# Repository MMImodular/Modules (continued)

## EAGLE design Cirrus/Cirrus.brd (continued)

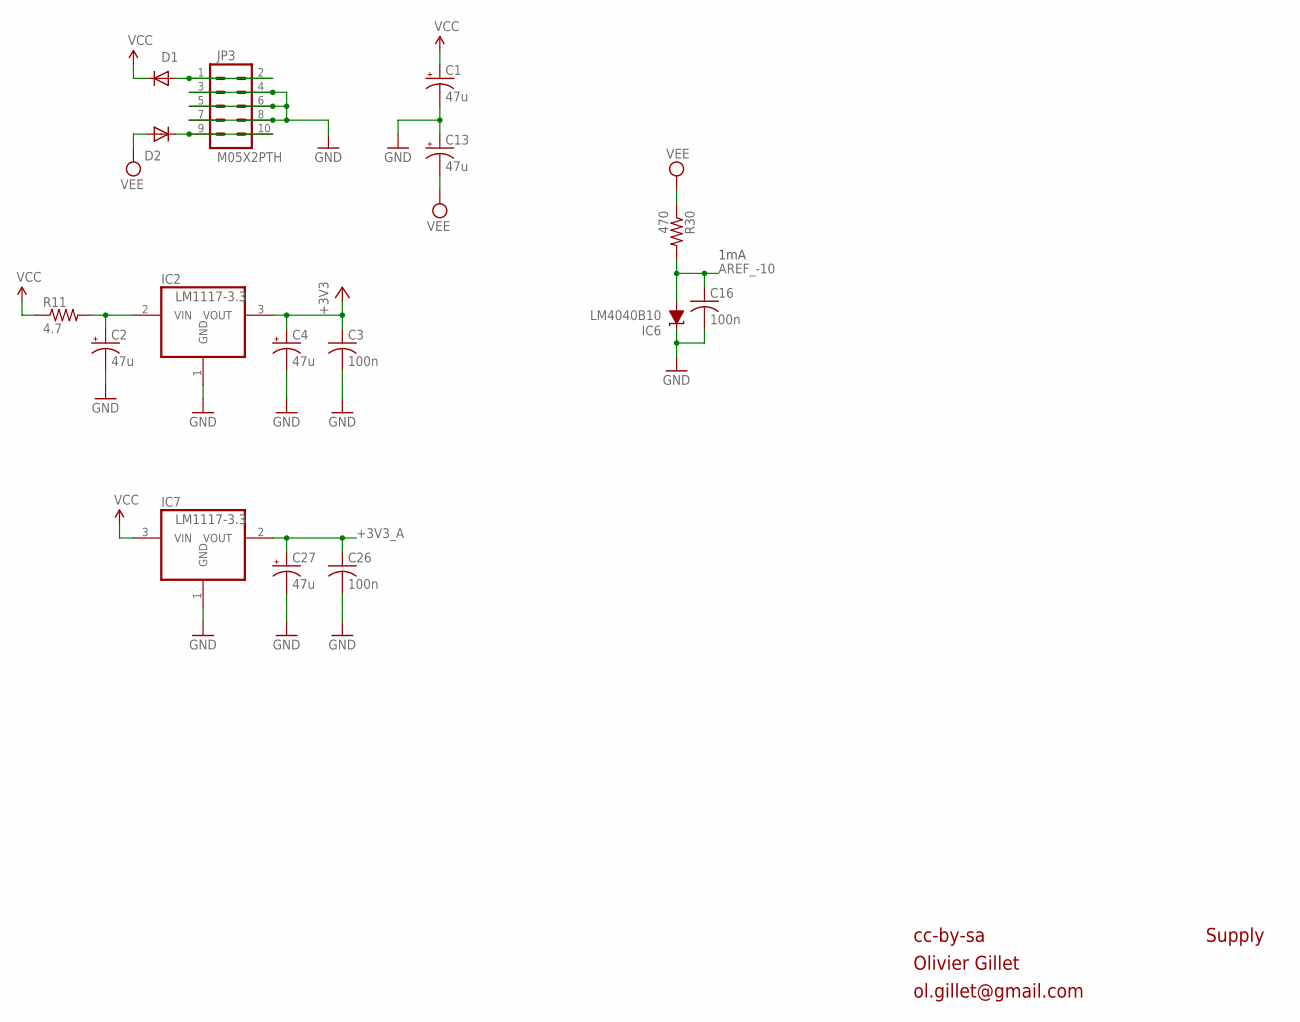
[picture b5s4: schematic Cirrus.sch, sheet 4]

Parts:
C1, C2, C4, C13, C27: 47u; PANASONIC_D
C3, C16, C26: 100n; C0603
D1, D2: 1N5819HW; SOD123
IC2: LM1117-3.3; TO252
IC6: LM4040B10; DBZ_R-PDSO-G3
IC7: LM1117-3.3; SOT223
JP3: M05X2PTH; AVR_ICSP
R11: 4.7; R1206
R30: 470; R0603

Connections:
+3V3: C3.1, C4.+, IC2.3 (VOUT); also elsewhere on the board
+3V3_A: C26.1, C27.+, IC7.2 (VOUT); also elsewhere on the board
AREF_-10: C16.1, IC6.2 (A), R30.2; also elsewhere on the board
GND: C1.-, C2.-, C3.2, C4.-, C13.+, C16.2, C26.2, C27.-, IC2.1 (GND), IC6.1 (C), IC7.1 (GND), JP3.3, JP3.4, JP3.5, JP3.6, JP3.7, JP3.8; also elsewhere on the board
unnamed: C2.+, IC2.2 (VIN), R11.2
unnamed: D1.A, JP3.1, JP3.2
unnamed: D2.C, JP3.9, JP3.10
VCC: C1.+, D1.C, IC7.3 (VIN), R11.1; also elsewhere on the board
VEE: C13.-, D2.A, R30.1; also elsewhere on the board

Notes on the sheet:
1mA
cc-by-sa
Olivier Gillet
ol.gillet@gmail.com
Supply

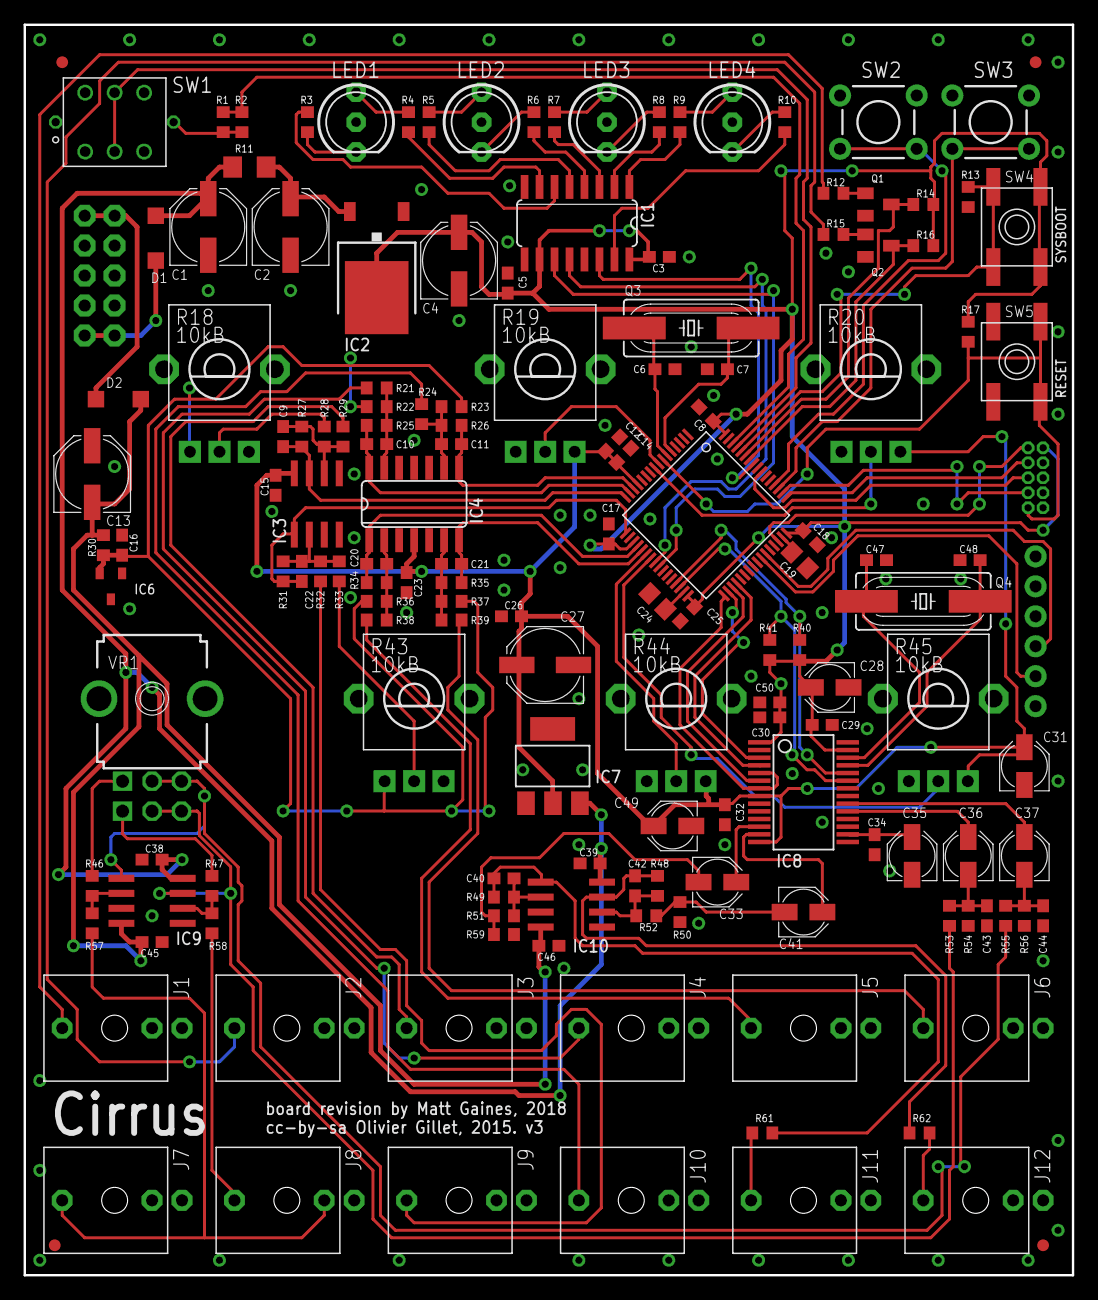
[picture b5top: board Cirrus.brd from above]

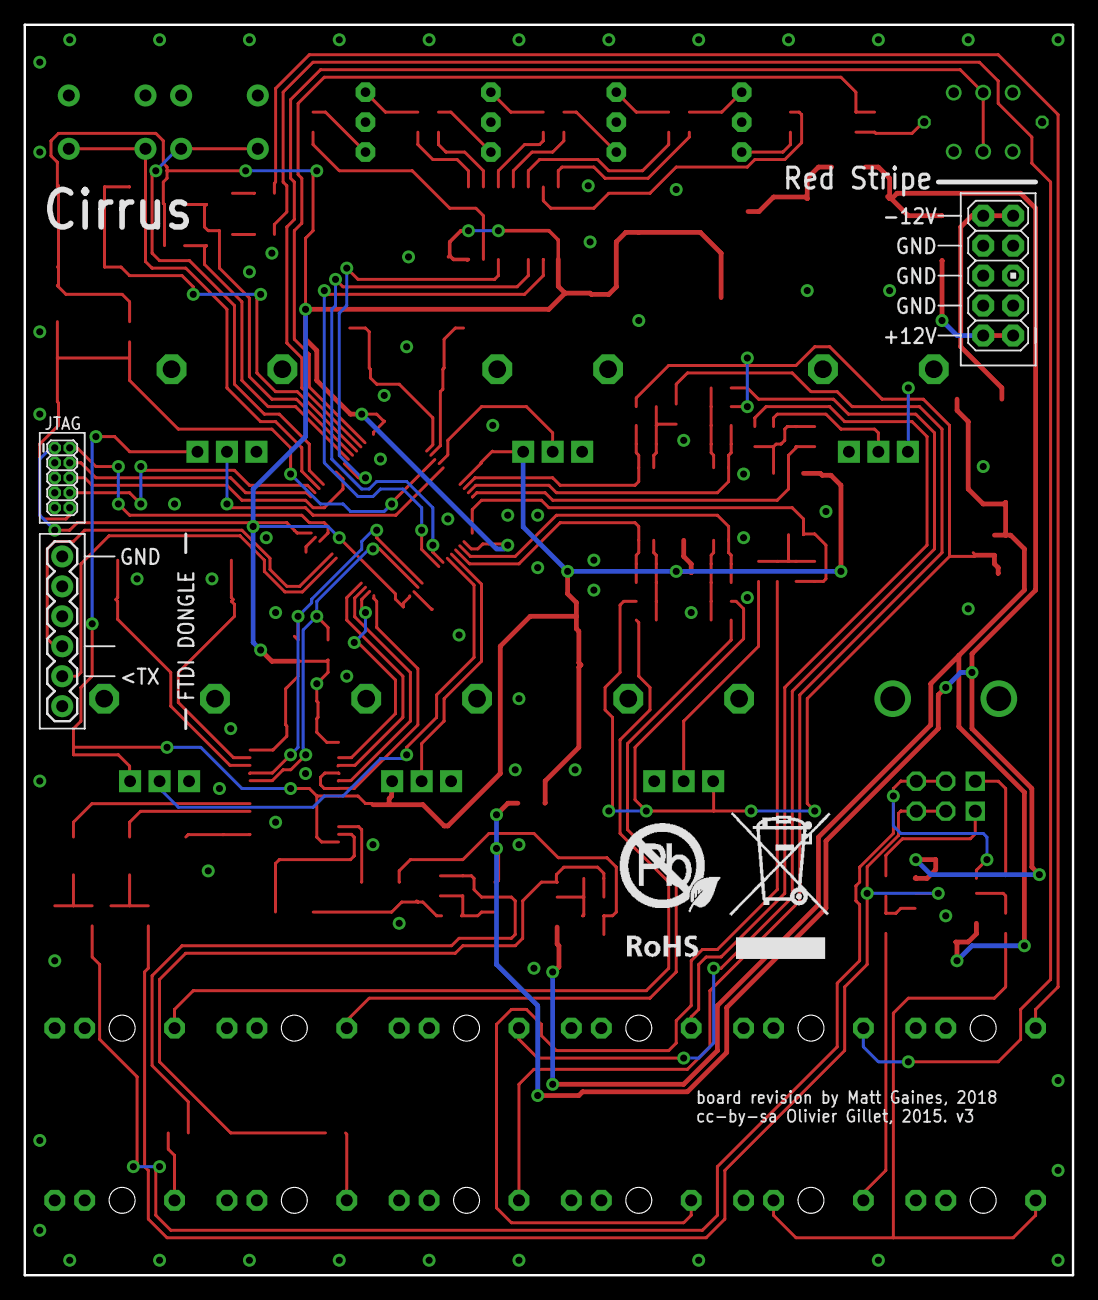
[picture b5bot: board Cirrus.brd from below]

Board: 2 copper layers, 88.9 x 106.0 mm, 156 parts (4 on the bottom side), 106 nets.

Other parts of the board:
U$2: ROHS_BIG

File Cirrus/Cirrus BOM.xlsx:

Qty | Value | Device | Package | Parts | Description | SPICEPREFIX | Column1
2 |  | EVQQ2 | EVQ-Q2 | SW4, SW5 | SMT 6mm switch, EVQQ2 series
1 |  | M06SIP | 1X06 | JP1 | Header 6
2 |  | TAC_SWITCHPTH | TACTILE-PTH | SW2, SW3 | Momentary Switch
2 | 1.0k | R-US_R0603 | R0603 | R61, R62 | RESISTOR, American symbol
8 | 100k | R-US_R0603 | R0603 | R12, R15, R21, R24, R29, R32, R38, R39 | RESISTOR, American symbol
19 | 100n | C-USC0603 | C0603 | C3, C5, C8, C14, C15, C16, C17, C18, C23, C25, C26, C29, C30, C32, C34, C38, C3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 | CAPACITOR, American symbol
4 | 10k | R-US_R0603 | R0603 | R13, R14, R16, R17 | RESISTOR, American symbol
6 | 10kB | POT_USVERTICAL_PS | ALPS_POT_VERTICAL_PS | R18, R19, R20, R43, R44, R45
7 | 10u | CPOL-USB | PANASONIC_B | C28, C31, C33, C35, C36, C37, C41 | POLARIZED CAPACITOR, American symbol
1 | 10u | CPOL-USB | PANASONIC_B | C49 | POLARIZED CAPACITOR, American symbol | C
1 | 12.288MHz | CRYSTALHC49UP | HC49UP | Q4 | CRYSTAL
1 | 180k | R-US_R0603 | R0603 | R36 | RESISTOR, American symbol
6 | 18p | C-USC0603 | C0603 | C6, C7, C40, C42, C47, C48 | CAPACITOR, American symbol
2 | 1N5819HW | DIODE-SOD123 | SOD123 | D1, D2 | DIODE
6 | 1n | C-USC0603 | C0603 | C9, C10, C11, C20, C21, C22 | CAPACITOR, American symbol
2 | 1u | C-USC0603 | C0603 | C12, C50 | CAPACITOR, American symbol
2 | 2.2k | R-US_R0603 | R0603 | R40, R41 | RESISTOR, American symbol
2 | 2.2u | C-USC0805 | C0805 | C19, C24 | CAPACITOR, American symbol
5 | 200k | R-US_R0603 | R0603 | R22, R23, R28, R33, R37 | RESISTOR, American symbol
2 | 220p | C-USC0603 | C0603 | C43, C44 | CAPACITOR, American symbol
2 | 22k | R-US_R0603 | R0603 | R57, R58 | RESISTOR, American symbol
2 | 3.3k | R-US_R0603 | R0603 | R46, R47 | RESISTOR, American symbol
3 | 33k | R-US_R0603 | R0603 | R25, R26, R35 | RESISTOR, American symbol
4 | 39k | R-US_R0603 | R0603 | R48, R49, R50, R59 | RESISTOR, American symbol
1 | 4.7 | R-US_R1206 | R1206 | R11 | RESISTOR, American symbol
1 | 470 | R-US_R0603 | R0603 | R30 | RESISTOR, American symbol
1 | 47k | R-US_R0603 | R0603 | R34 | RESISTOR, American symbol
5 | 47u | CPOL-USD | PANASONIC_D | C1, C2, C4, C13, C27 | POLARIZED CAPACITOR, American symbol
6 | 5.6k | R-US_R0603 | R0603 | R51, R52, R53, R54, R55, R56 | RESISTOR, American symbol
1 | 50kA | ALPHA-9MM-DUALPOT | DUAL_9MM_SNAP-IN_POT | VR1 | 9mm vertical snap-in pot, Alpha / Panasonic style, with a connection to the met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
2 | 66.5k | R-US_R0603 | R0603 | R27, R31 | RESISTOR, American symbol
10 | 68 | R-US_R0603 | R0603 | R1, R2, R3, R4, R5, R6, R7, R8, R9, R10 | RESISTOR, American symbol
1 | 74HC595D | 74HC595D | SO16 | IC1 | 8-bit SHIFT REGISTER, output latch
1 | 8MHz | CRYSTALHC49UP | HC49UP | Q3 | CRYSTAL
4 | FIDUCIAL1X2 | FIDUCIAL1X2 | FIDUCIAL-1X2 | F1, F2, F3, F4 | Fiducial Alignment Points
1 | LM1117-3.3 | REG1117 | SOT223 | IC7 | 800mA and 1A Low Dropout (LDO) Positive Regulator
1 | LM1117-3.3 | REG1117T | TO252 | IC2 | 800mA and 1A Low Dropout (LDO) Positive Regulator
1 | LM4040B10 | LM4041B12DBZ | DBZ_R-PDSO-G3 | IC6 | PRECISION MICROPOWER SHUNT VOLTAGE REFERENCE
1 | LP4OA1PBCT | LP4OA1PBCT | LP4OA1PBCT | SW1
1 | M05X2MINIJTAG | M05X2MINIJTAG | 2X5-1.27 | JP2 | Header 5x2
1 | M05X2PTH | M05X2PTH | AVR_ICSP | JP3 | Header 5x2
1 | MCP6002 | TL072D | SO08 | IC3 | OP AMP
1 | MCP6004 | TL074D | SO14 | IC4 | OP AMP
2 | MMBT3904 | MMBT3904LT1-NPN-SOT23-BEC | SOT23-BEC | Q1, Q2 | NPN Transistror
12 | PJ301_THONKICONN6 | PJ301_THONKICONN6 | WQP_PJ_301M6 | J1, J2, J3, J4, J5, J6, J7, J8, J9, J10, J11, J12
1 | STM32F405RGT6 | STM32F20X | TQFP-10X10-64 | IC5
2 | TL072D | TL072D | SO08 | IC9, IC10 | OP AMP
1 | WM8731 | WM8731 | SSOP28 | IC8
4 | WP59EGW | LED-BICOLOR-THROUGHHOLE5MM | LED-BICOLOR-THROUGHHOLE-5MM | LED1, LED2, LED3, LED4

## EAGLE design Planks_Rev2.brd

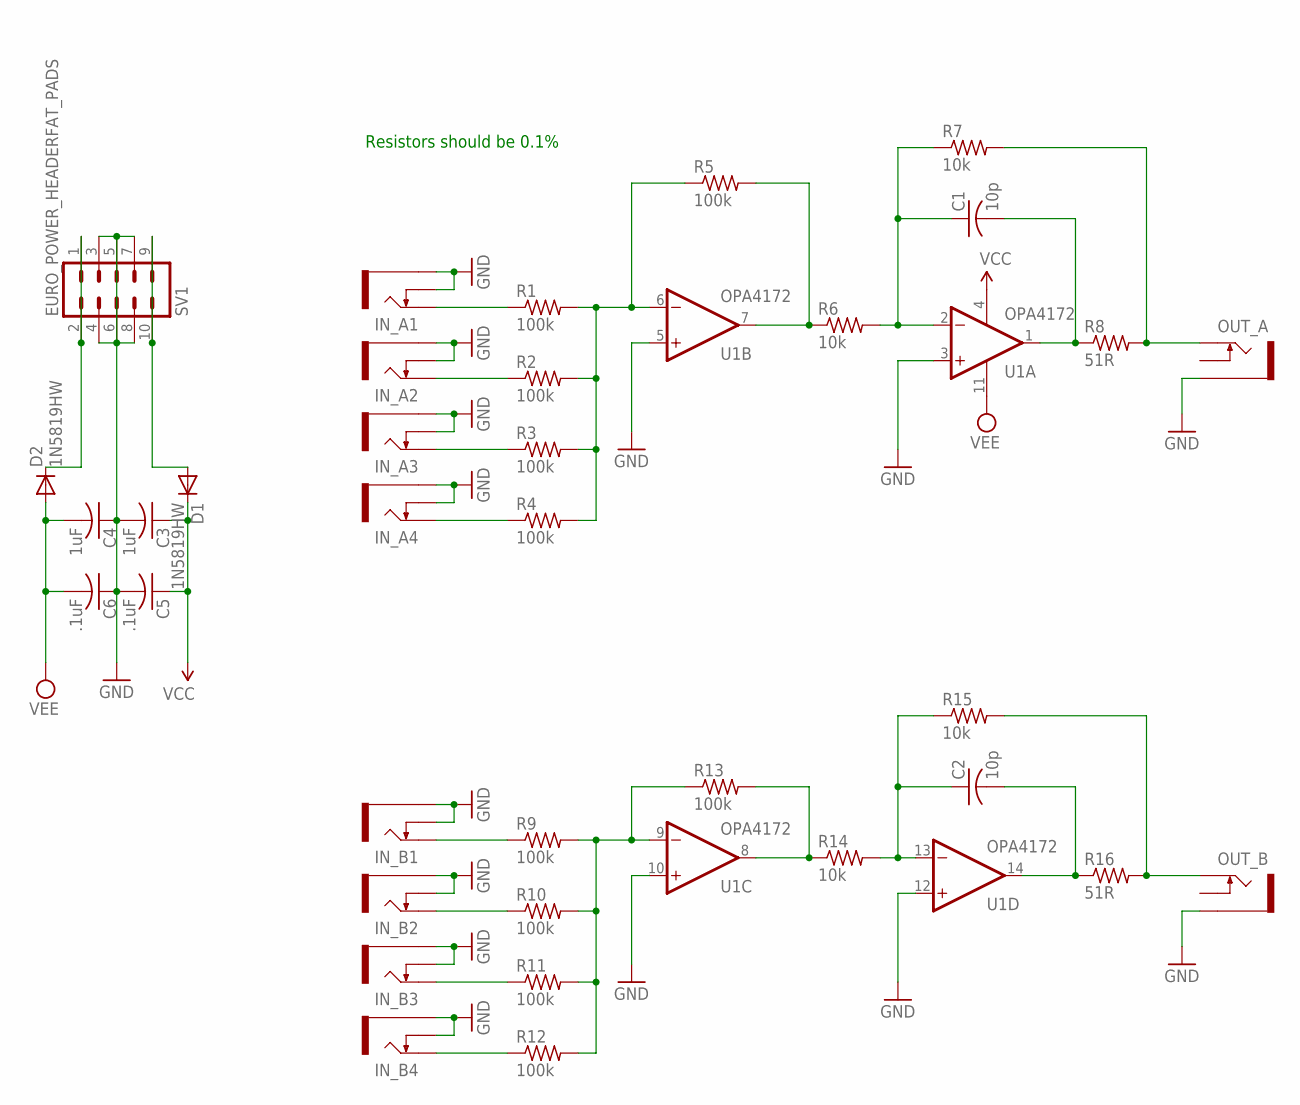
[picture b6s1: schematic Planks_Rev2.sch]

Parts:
C1, C2: 10p; C0603
C3, C4: 1uF; C0805
C5, C6: .1uF; C0603
D1, D2: 1N5819HW; SOD123
IN_A1, IN_A2, IN_A3, IN_A4: THONKICONNNEW; WQP-PJ301M-12_JACK
IN_B1, IN_B2, IN_B3, IN_B4: THONKICONNNEW; WQP-PJ301M-12_JACK
OUT_A: THONKICONNNEW; WQP-PJ301M-12_JACK
OUT_B: THONKICONNNEW; WQP-PJ301M-12_JACK
R1, R2, R3, R4, R5, R9, R10, R11, R12, R13: 100k; R0603
R6, R7, R14, R15: 10k; R0603
R8, R16: 51R; R0603
SV1: EURO_POWER_HEADERFAT_PADS; EURO_PWR_HEADER_FAT
U1: OPA4172; SO14

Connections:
GND: C3.2, C4.1, C5.2, C6.1, IN_A1.P$2_SWITCH (SWITCH), IN_A1.P$3_SLEEVE (SLEEVE), IN_A2.P$2_SWITCH (SWITCH), IN_A2.P$3_SLEEVE (SLEEVE), IN_A3.P$2_SWITCH (SWITCH), IN_A3.P$3_SLEEVE (SLEEVE), IN_A4.P$2_SWITCH (SWITCH), IN_A4.P$3_SLEEVE (SLEEVE), IN_B1.P$2_SWITCH (SWITCH), IN_B1.P$3_SLEEVE (SLEEVE), IN_B2.P$2_SWITCH (SWITCH), IN_B2.P$3_SLEEVE (SLEEVE), IN_B3.P$2_SWITCH (SWITCH), IN_B3.P$3_SLEEVE (SLEEVE), IN_B4.P$2_SWITCH (SWITCH), IN_B4.P$3_SLEEVE (SLEEVE), OUT_A.P$3_SLEEVE (SLEEVE), OUT_B.P$3_SLEEVE (SLEEVE), SV1.3, SV1.4, SV1.5, SV1.6, SV1.7, SV1.8, U1.3 (+IN), U1.5 (+IN), U1.10 (+IN), U1.12 (+IN)
unnamed: IN_A1.P$1_TIP (TIP), R1.1
unnamed: IN_A4.P$1_TIP (TIP), R4.1
unnamed: IN_A3.P$1_TIP (TIP), R3.1
unnamed: IN_A2.P$1_TIP (TIP), R2.1
unnamed: R1.2, R2.2, R3.2, R4.2, R5.1, U1.6 (-IN)
unnamed: IN_B1.P$1_TIP (TIP), R9.1
unnamed: R5.2, R6.1, U1.7 (OUT)
unnamed: C1.1, R6.2, R7.1, U1.2 (-IN)
unnamed: IN_B4.P$1_TIP (TIP), R12.1
unnamed: C1.2, R8.1, U1.1 (OUT)
unnamed: OUT_A.P$1_TIP (TIP), R7.2, R8.2
unnamed: IN_B3.P$1_TIP (TIP), R11.1
unnamed: IN_B2.P$1_TIP (TIP), R10.1
unnamed: R9.2, R10.2, R11.2, R12.2, R13.1, U1.9 (-IN)
unnamed: R13.2, R14.1, U1.8 (OUT)
unnamed: C2.1, R14.2, R15.1, U1.13 (-IN)
unnamed: D1.A, SV1.9, SV1.10
unnamed: D2.C, SV1.1, SV1.2
unnamed: OUT_B.P$1_TIP (TIP), R15.2, R16.2
unnamed: C2.2, R16.1, U1.14 (OUT)
VCC: C3.1, C5.1, D1.C, U1.4 (V+)
VEE: C4.2, C6.2, D2.A, U1.11 (V-)

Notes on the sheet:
Resistors should be 0.1%

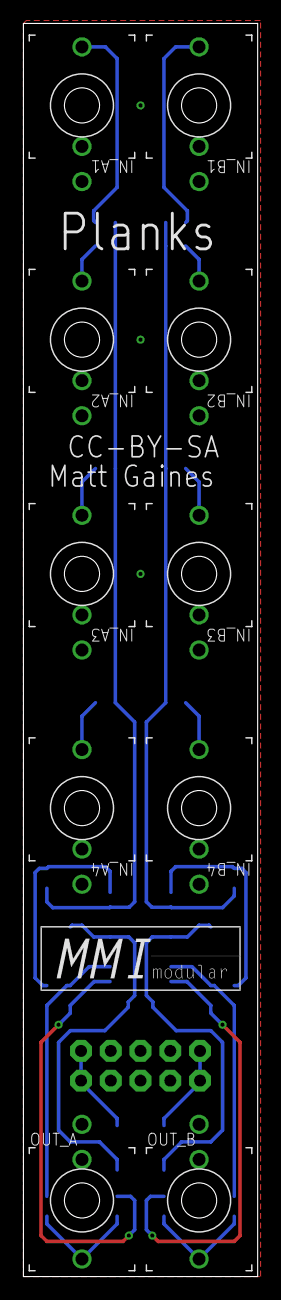
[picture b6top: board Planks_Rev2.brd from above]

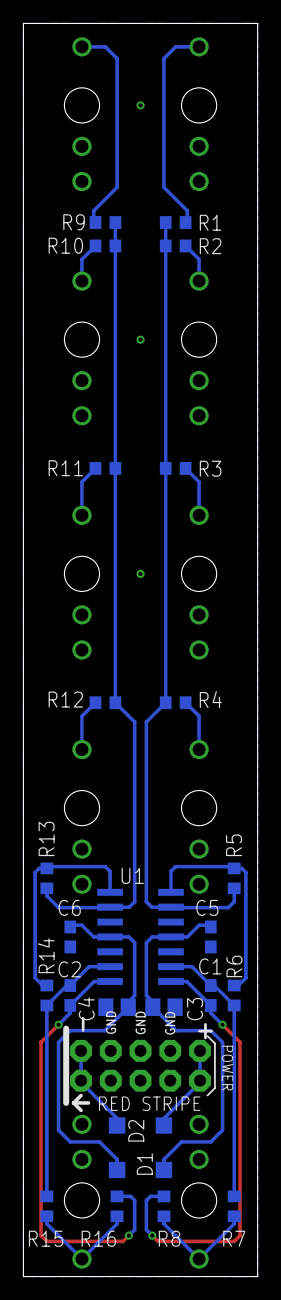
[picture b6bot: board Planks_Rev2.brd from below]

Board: 2 copper layers, 20.0 x 107.0 mm, 36 parts (26 on the bottom side), 23 nets.

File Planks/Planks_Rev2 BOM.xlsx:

Value | Package | Tolerance | Parts
100k | R0603 | 1E-3 | R1, R2, R3, R4, R5, R9, R10, R11, R12, R13
10k | R0603 | 1E-3 | R6, R7, R14, R15
51R | R0603 | 0.01 | R8, R16
1uF | C0805 | 0.1 | C3, C4
0.1uF | C0603 | 0.1 | C5, C6
10pF | C0603 | 0.05 | C1, C2
1N5819HW | SOD123 |  | D1, D2
OPA4172 | SO14 |  | U1
Thonkiconn | Thonkiconn |  | IN_A1, IN_A2, IN_A3, IN_A4, IN_B1, IN_B2, IN_B3, IN_B4, OUT_A, OUT_B

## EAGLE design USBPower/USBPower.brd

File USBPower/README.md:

# USB Power

* Based on Tom Whitwell's StupidUSBPower
* Integrated better DC-DC converter and removed frivolous features
* Rated to 416mA, capable of 110 ~ 140% overload with automatic recovery once fault condition is removed

This power supply is a low cost and low profile way to power a small lunchbox eurorack system. It is also a useful power supply for testing newly built modules outside of a larger system, especially if you must commute to your workspace.

___

The Meanwell DC-DC converter used in this power supply has a few important specifications to consider.
* Under full load, the DC-DC converter will draw upwards of 2300mA direct from your USB power brick. Make sure it can supply ~3A if you plan on running your PSU near the max current spec.
* Maximum load capacitance is 440uF per output. Approaching this may cause instability upon power-up. This needs more investigation on my part so I will update this list if I figure out more specific cases of instability.
* There is an under-voltage lockout implemented in this converter. It takes 4.4V to start the converter and it will shut down if it goes below 4.2V. This important because some users have experienced instability with USB cables that are incapable of supplying power. Voltage drop across the cable may be enough to go below 4.2V and result in a boot loop.

___
**Known module incompatibilities**

These are modules that people have plugged in and run in to boot looping issues with, despite the PSU operating normally otherwise. I do not have the ability to test each and every module that comes up, but if you own any of these I encourage testing it for yourself and sending me a message or email detailing what you found.

* Synthrotek 308 Distortion
* Jomox ModBase 09
* Strymon Magneto (works solo, but loops if other modules are present)

___
**Where to buy PCBs** 

* [Modular Addict](https://modularaddict.com/mmi-usbpower-pcb)

* [Pusherman](https://pushermanproductions.com/product/mmi-modular-usb-power-supply/) (this is the best spot to pick one up if you live outside the USA)

* [Directly from me!](https://reverb.com/item/13361422-mmi-modular-eurorack-usb-power-supply-pcb-only)

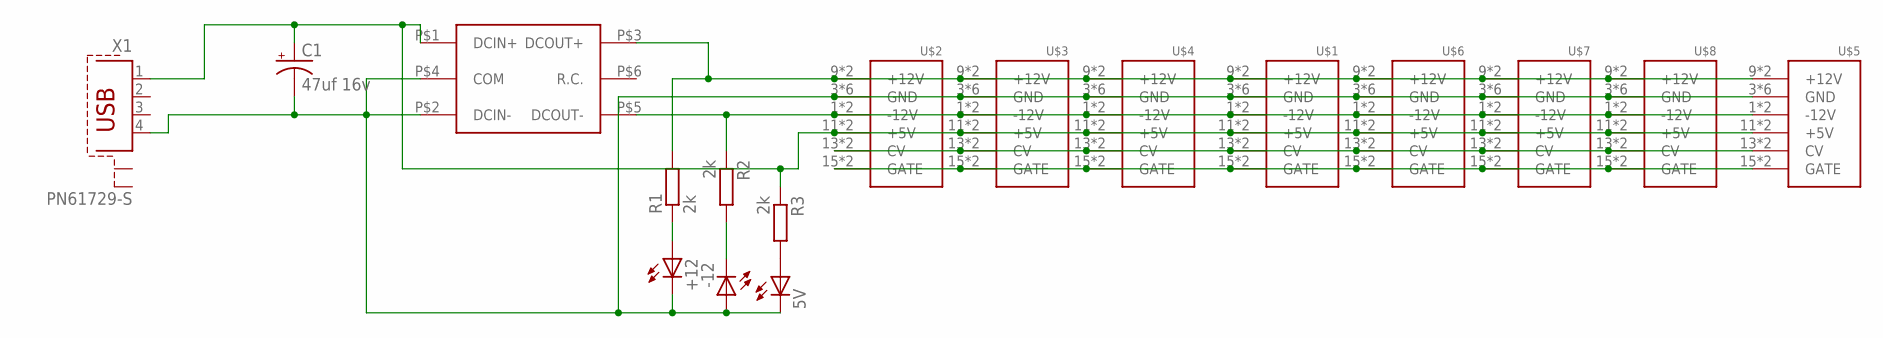
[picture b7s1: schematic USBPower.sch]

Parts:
5V: LED3MM
+12: LED3MM
-12: LED3MM
C1: 47uf 16v; 050_020
R1, R2, R3: 2k; 7MM_RESISTOR
U$1, U$2, U$3, U$4, U$5, U$6, U$7, U$8: POWER; POWER_16
U$9: DKM-10; 1X1
X1: PN61729-S

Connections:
5V: C1.+, R3.1, U$1.11 (+5V), U$1.12 (+5V), U$2.11 (+5V), U$2.12 (+5V), U$3.11 (+5V), U$3.12 (+5V), U$4.11 (+5V), U$4.12 (+5V), U$5.11 (+5V), U$5.12 (+5V), U$6.11 (+5V), U$6.12 (+5V), U$7.11 (+5V), U$7.12 (+5V), U$8.11 (+5V), U$8.12 (+5V), U$9.P$1 (DCIN+), X1.1
+12V: R1.2, U$1.9 (+12V), U$1.10 (+12V), U$2.9 (+12V), U$2.10 (+12V), U$3.9 (+12V), U$3.10 (+12V), U$4.9 (+12V), U$4.10 (+12V), U$5.9 (+12V), U$5.10 (+12V), U$6.9 (+12V), U$6.10 (+12V), U$7.9 (+12V), U$7.10 (+12V), U$8.9 (+12V), U$8.10 (+12V), U$9.P$3 (DCOUT+)
-12V: R2.1, U$1.1 (-12V), U$1.2 (-12V), U$2.1 (-12V), U$2.2 (-12V), U$3.1 (-12V), U$3.2 (-12V), U$4.1 (-12V), U$4.2 (-12V), U$5.1 (-12V), U$5.2 (-12V), U$6.1 (-12V), U$6.2 (-12V), U$7.1 (-12V), U$7.2 (-12V), U$8.1 (-12V), U$8.2 (-12V), U$9.P$5 (DCOUT-)
COM: 5V.K (C), +12.K (C), -12.A, C1.-, U$1.3 (GND), U$1.4 (GND), U$1.5 (GND), U$1.6 (GND), U$1.7 (GND), U$1.8 (GND), U$2.3 (GND), U$2.4 (GND), U$2.5 (GND), U$2.6 (GND), U$2.7 (GND), U$2.8 (GND), U$3.3 (GND), U$3.4 (GND), U$3.5 (GND), U$3.6 (GND), U$3.7 (GND), U$3.8 (GND), U$4.3 (GND), U$4.4 (GND), U$4.5 (GND), U$4.6 (GND), U$4.7 (GND), U$4.8 (GND), U$5.3 (GND), U$5.4 (GND), U$5.5 (GND), U$5.6 (GND), U$5.7 (GND), U$5.8 (GND), U$6.3 (GND), U$6.4 (GND), U$6.5 (GND), U$6.6 (GND), U$6.7 (GND), U$6.8 (GND), U$7.3 (GND), U$7.4 (GND), U$7.5 (GND), U$7.6 (GND), U$7.7 (GND), U$7.8 (GND), U$8.3 (GND), U$8.4 (GND), U$8.5 (GND), U$8.6 (GND), U$8.7 (GND), U$8.8 (GND), U$9.P$2 (DCIN-), U$9.P$4 (COM), X1.4
unnamed: -12.K (C), R2.2
unnamed: U$1.13 (CV), U$1.14 (CV), U$2.13 (CV), U$2.14 (CV), U$3.13 (CV), U$3.14 (CV), U$4.13 (CV), U$4.14 (CV), U$5.13 (CV), U$5.14 (CV), U$6.13 (CV), U$6.14 (CV), U$7.13 (CV), U$7.14 (CV), U$8.13 (CV), U$8.14 (CV)
unnamed: U$1.15 (GATE), U$1.16 (GATE), U$2.15 (GATE), U$2.16 (GATE), U$3.15 (GATE), U$3.16 (GATE), U$4.15 (GATE), U$4.16 (GATE), U$5.15 (GATE), U$5.16 (GATE), U$6.15 (GATE), U$6.16 (GATE), U$7.15 (GATE), U$7.16 (GATE), U$8.15 (GATE), U$8.16 (GATE)
unnamed: 5V.A, R3.2
unnamed: +12.A, R1.1

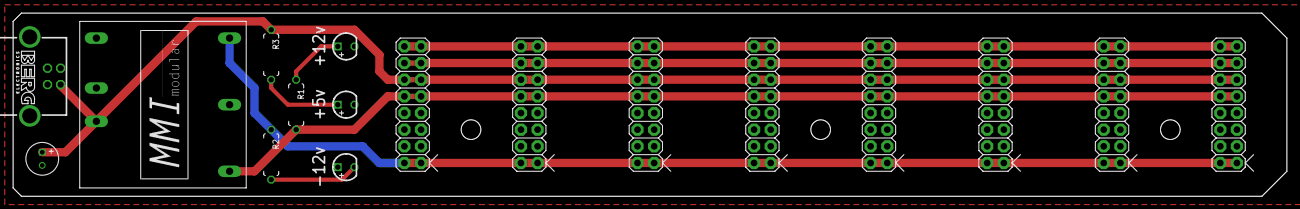
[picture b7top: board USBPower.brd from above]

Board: 2 copper layers, 194.3 x 27.9 mm, 17 parts (0 on the bottom side), 9 nets.

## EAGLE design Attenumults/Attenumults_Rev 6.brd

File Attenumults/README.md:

# Attenumults
* Dual 1:4 buffered multiple that has individual attenuverters on each output
* Dual 3:1 unity mixers are at the bottom to provide extra utility

Attenumults allows you to control a number of parameters at once in different directions and magnitudes, a useful utility module and a perfect complement to Maths or Rampage.

PCB/panel sets are available at [Modular Addict](https://modularaddict.com/mmi-attenumults-pcbpanel) and [Pusherman](https://pushermanproductions.com/product/bam-attenumult-unity-mix/)

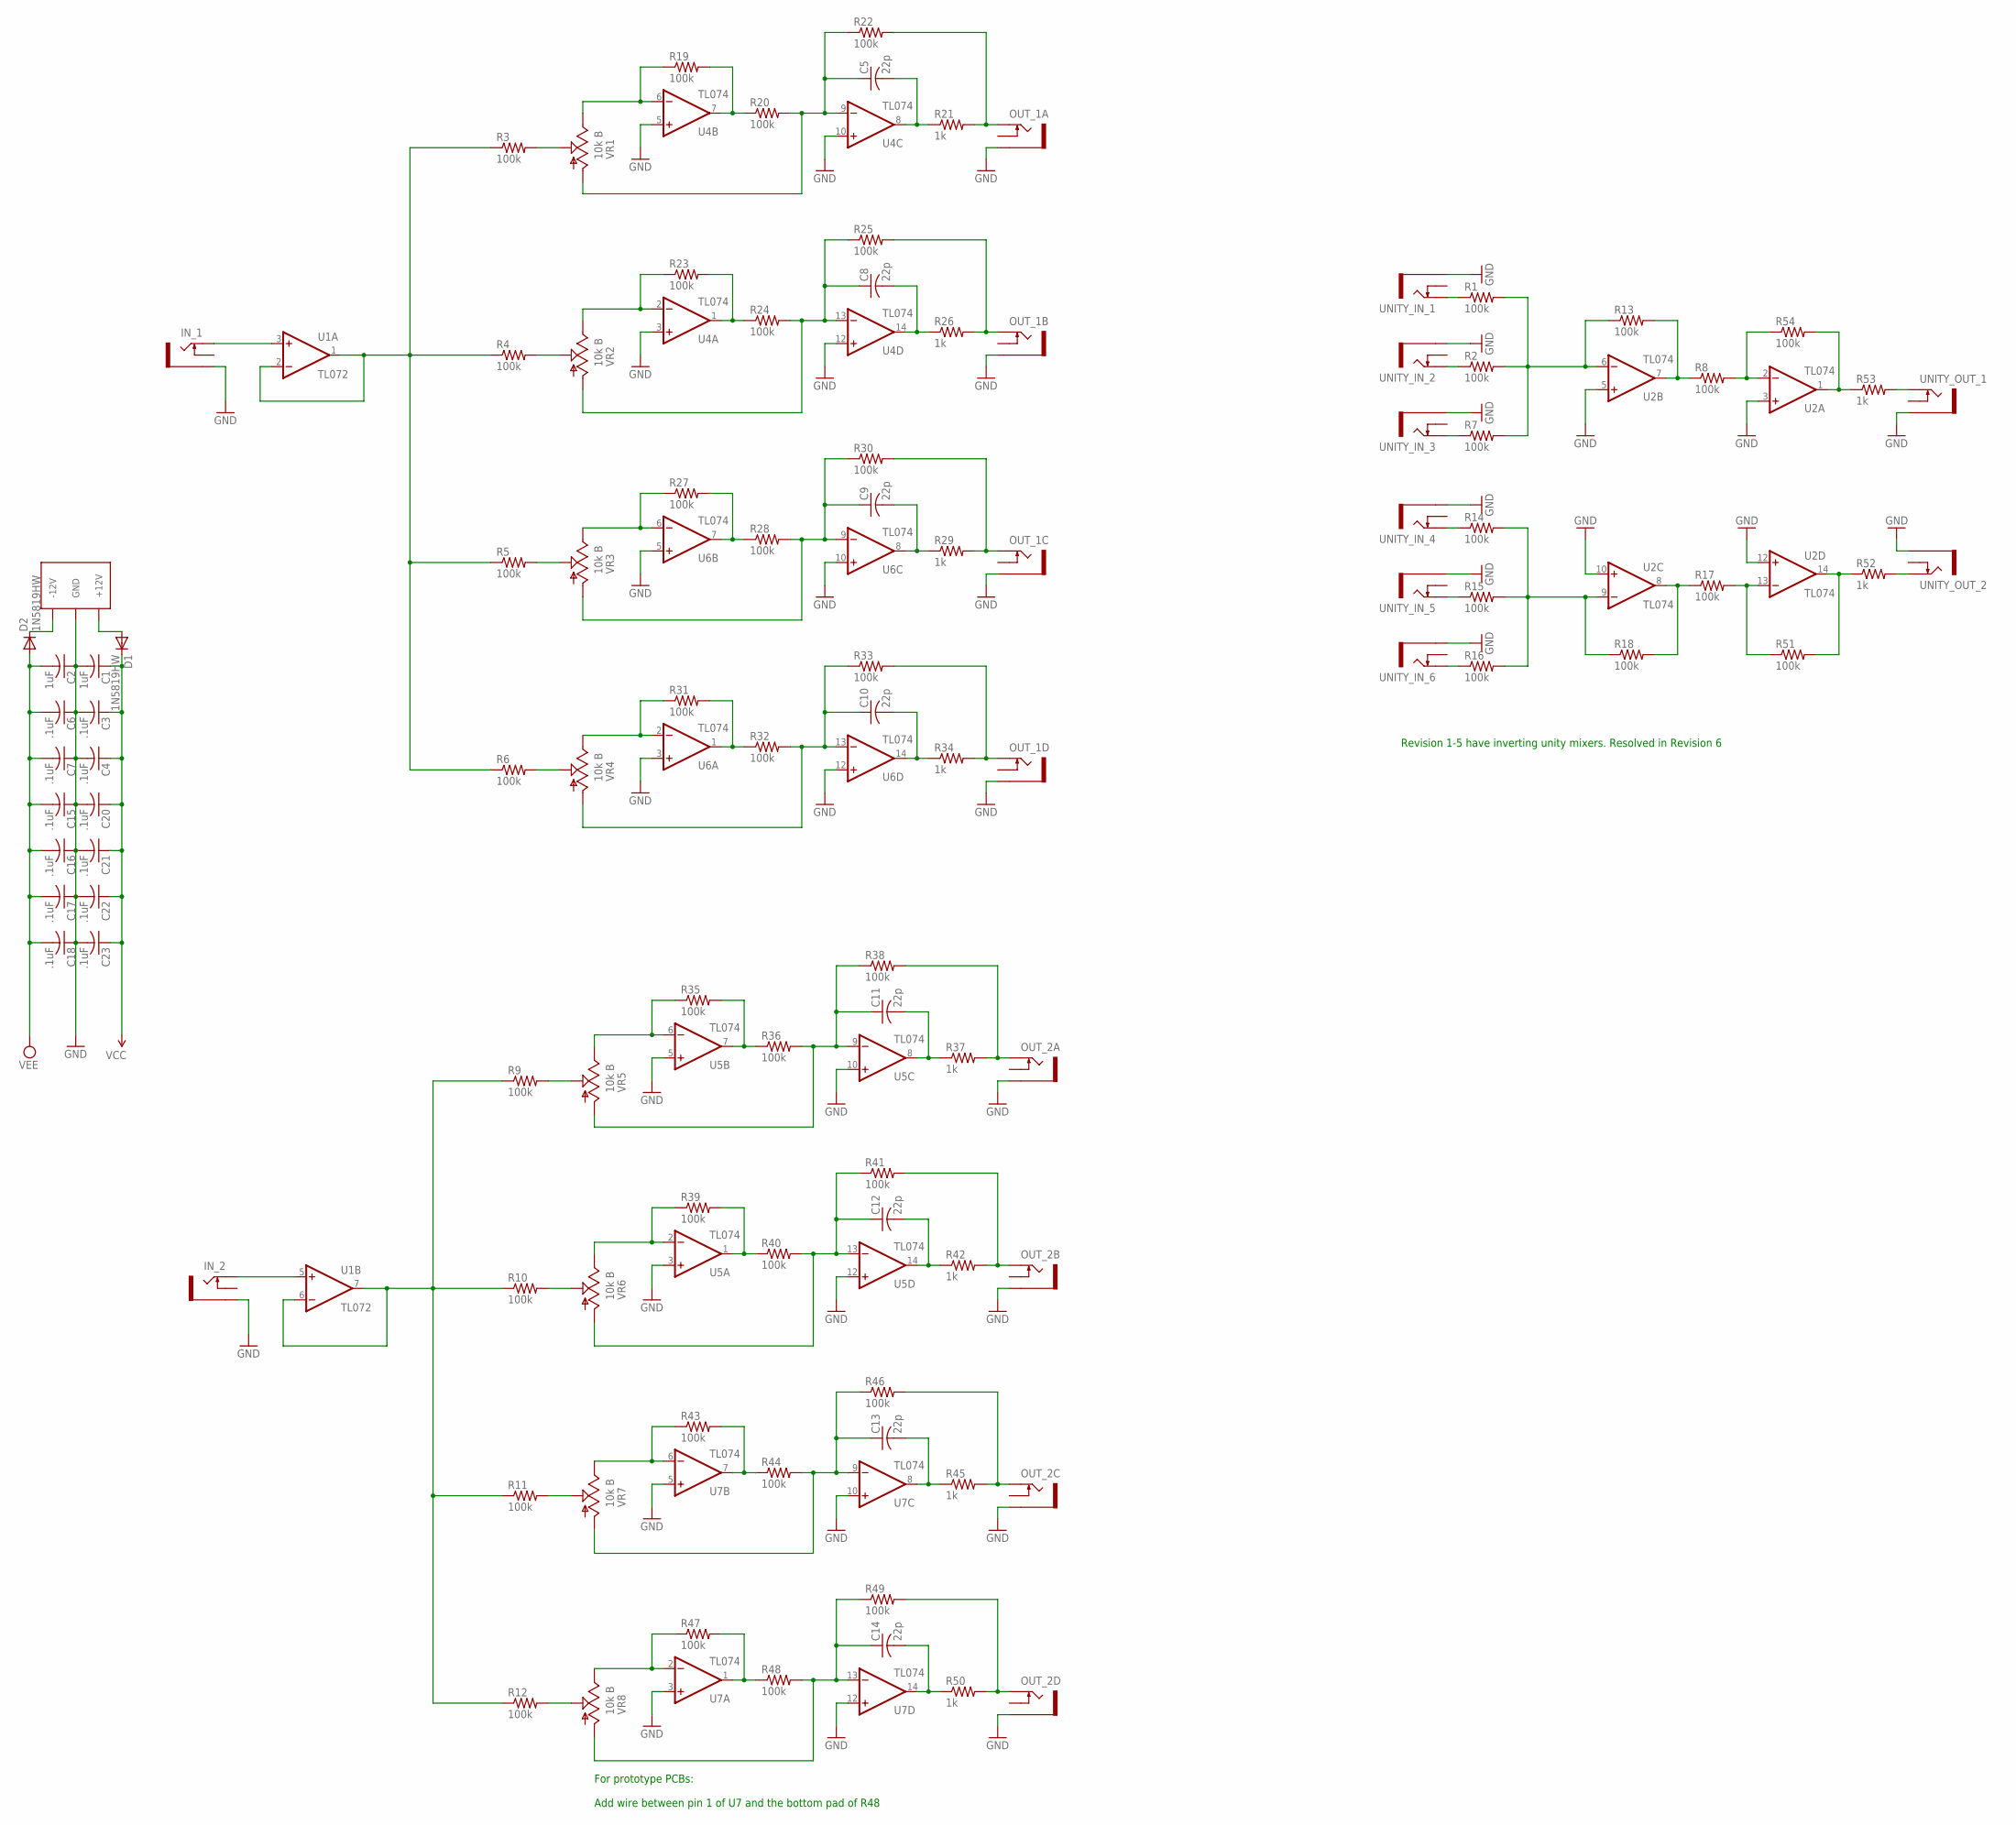
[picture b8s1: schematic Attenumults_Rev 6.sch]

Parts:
C1, C2: 1uF; C0805
C3, C4, C6, C7, C15, C16, C17, C18, C20, C21, C22, C23: .1uF; C0805
C5, C8, C9, C10, C11, C12, C13, C14: 22p; C0805
D1, D2: 1N5819HW; SOD123
IN_1, IN_2: THONKICONNNEW; WQP-PJ301M-12_JACK
OUT_1A, OUT_1B, OUT_1C, OUT_1D, OUT_2A, OUT_2B, OUT_2C, OUT_2D: THONKICONNNEW; WQP-PJ301M-12_JACK
R1, R2, R3, R4, R5, R6, R7, R8, R9, R10, R11, R12, R13, R14, R15, R16, R17, R18, R19, R20, R22, R23, R24, R25, R27, R28, R30, R31, R32, R33, R35, R36, R38, R39, R40, R41, R43, R44, R46, R47, R48, R49, R51, R54: 100k; R0805
R21, R26, R29, R34, R37, R42, R45, R50, R52, R53: 1k; R0805
U1: TL072; SO08
U2, U4, U5, U6, U7: TL074; SO14
U$1: EURO_POWER_LOCK; EURO_PWR_HEADER_LOCK
UNITY_IN_1, UNITY_IN_2, UNITY_IN_3, UNITY_IN_4, UNITY_IN_5, UNITY_IN_6: THONKICONNNEW; WQP-PJ301M-12_JACK
UNITY_OUT_1, UNITY_OUT_2: THONKICONNNEW; WQP-PJ301M-12_JACK
VR1, VR2, VR3, VR4, VR5, VR6, VR7, VR8: 10k B; ALPS_POT_VERTICAL_PS

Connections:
GND: C1.2, C2.1, C3.2, C4.2, C6.1, C7.1, C15.1, C16.1, C17.1, C18.1, C20.2, C21.2, C22.2, C23.2, IN_1.P$3_SLEEVE (SLEEVE), IN_2.P$3_SLEEVE (SLEEVE), OUT_1A.P$3_SLEEVE (SLEEVE), OUT_1B.P$3_SLEEVE (SLEEVE), OUT_1C.P$3_SLEEVE (SLEEVE), OUT_1D.P$3_SLEEVE (SLEEVE), OUT_2A.P$3_SLEEVE (SLEEVE), OUT_2B.P$3_SLEEVE (SLEEVE), OUT_2C.P$3_SLEEVE (SLEEVE), OUT_2D.P$3_SLEEVE (SLEEVE), U2.3 (+IN), U2.5 (+IN), U2.10 (+IN), U2.12 (+IN), U4.3 (+IN), U4.5 (+IN), U4.10 (+IN), U4.12 (+IN), U5.3 (+IN), U5.5 (+IN), U5.10 (+IN), U5.12 (+IN), U6.3 (+IN), U6.5 (+IN), U6.10 (+IN), U6.12 (+IN), U7.3 (+IN), U7.5 (+IN), U7.10 (+IN), U7.12 (+IN), U$1.GND1 (GND), U$1.GND2 (GND), U$1.GND3 (GND), U$1.GND4 (GND), U$1.GND5 (GND), U$1.GND6 (GND), UNITY_IN_1.P$3_SLEEVE (SLEEVE), UNITY_IN_2.P$3_SLEEVE (SLEEVE), UNITY_IN_3.P$3_SLEEVE (SLEEVE), UNITY_IN_4.P$3_SLEEVE (SLEEVE), UNITY_IN_5.P$3_SLEEVE (SLEEVE), UNITY_IN_6.P$3_SLEEVE (SLEEVE), UNITY_OUT_1.P$3_SLEEVE (SLEEVE), UNITY_OUT_2.P$3_SLEEVE (SLEEVE)
unnamed: IN_1.P$1_TIP (TIP), U1.3 (+IN)
unnamed: R3.2, VR1.P$2 (S)
unnamed: R19.1, U4.6 (-IN), VR1.P$1 (E)
unnamed: R3.1, R4.1, R5.1, R6.1, U1.1 (OUT), U1.2 (-IN)
unnamed: R1.2, R2.2, R7.2, R13.1, U2.6 (-IN)
unnamed: IN_2.P$1_TIP (TIP), U1.5 (+IN)
unnamed: R19.2, R20.1, U4.7 (OUT)
unnamed: R9.1, R10.1, R11.1, R12.1, U1.6 (-IN), U1.7 (OUT)
unnamed: C5.1, R20.2, R22.1, U4.9 (-IN), VR1.P$3 (A)
unnamed: R8.2, R54.1, U2.2 (-IN)
unnamed: C5.2, R21.1, U4.8 (OUT)
unnamed: OUT_1A.P$1_TIP (TIP), R21.2, R22.2
unnamed: R4.2, VR2.P$2 (S)
unnamed: R23.1, U4.2 (-IN), VR2.P$1 (E)
unnamed: R7.1, UNITY_IN_3.P$1_TIP (TIP)
unnamed: R53.1, R54.2, U2.1 (OUT)
unnamed: R53.2, UNITY_OUT_1.P$1_TIP (TIP)
unnamed: R17.2, R51.1, U2.13 (-IN)
unnamed: R51.2, R52.1, U2.14 (OUT)
unnamed: R52.2, UNITY_OUT_2.P$1_TIP (TIP)
unnamed: R9.2, VR5.P$2 (S)
unnamed: R23.2, R24.1, U4.1 (OUT)
unnamed: R35.1, U5.6 (-IN), VR5.P$1 (E)
unnamed: C8.1, R24.2, R25.1, U4.13 (-IN), VR2.P$3 (A)
unnamed: R35.2, R36.1, U5.7 (OUT)
unnamed: C8.2, R26.1, U4.14 (OUT)
unnamed: C11.1, R36.2, R38.1, U5.9 (-IN), VR5.P$3 (A)
unnamed: OUT_1B.P$1_TIP (TIP), R25.2, R26.2
unnamed: R2.1, UNITY_IN_2.P$1_TIP (TIP)
unnamed: R1.1, UNITY_IN_1.P$1_TIP (TIP)
unnamed: R8.1, R13.2, U2.7 (OUT)
unnamed: R17.1, R18.2, U2.8 (OUT)
unnamed: R14.2, R15.2, R16.2, R18.1, U2.9 (-IN)
unnamed: R16.1, UNITY_IN_6.P$1_TIP (TIP)
unnamed: R15.1, UNITY_IN_5.P$1_TIP (TIP)
unnamed: R14.1, UNITY_IN_4.P$1_TIP (TIP)
unnamed: D1.A, U$1.POS1 (+12V), U$1.POS2 (+12V)
unnamed: D2.C, U$1.NEG1 (-12V), U$1.NEG2 (-12V)
unnamed: R27.1, U6.6 (-IN), VR3.P$1 (E)
unnamed: R27.2, R28.1, U6.7 (OUT)
unnamed: C9.1, R28.2, R30.1, U6.9 (-IN), VR3.P$3 (A)
unnamed: C9.2, R29.1, U6.8 (OUT)
unnamed: OUT_1C.P$1_TIP (TIP), R29.2, R30.2
unnamed: R31.1, U6.2 (-IN), VR4.P$1 (E)
unnamed: R31.2, R32.1, U6.1 (OUT)
unnamed: C10.1, R32.2, R33.1, U6.13 (-IN), VR4.P$3 (A)
unnamed: C10.2, R34.1, U6.14 (OUT)
unnamed: OUT_1D.P$1_TIP (TIP), R33.2, R34.2
unnamed: C11.2, R37.1, U5.8 (OUT)
unnamed: R6.2, VR4.P$2 (S)
unnamed: R5.2, VR3.P$2 (S)
unnamed: OUT_2A.P$1_TIP (TIP), R37.2, R38.2
unnamed: R10.2, VR6.P$2 (S)
unnamed: R39.1, U5.2 (-IN), VR6.P$1 (E)
unnamed: R39.2, R40.1, U5.1 (OUT)
unnamed: C12.1, R40.2, R41.1, U5.13 (-IN), VR6.P$3 (A)
unnamed: C12.2, R42.1, U5.14 (OUT)
unnamed: OUT_2B.P$1_TIP (TIP), R41.2, R42.2
unnamed: R43.1, U7.6 (-IN), VR7.P$1 (E)
unnamed: R43.2, R44.1, U7.7 (OUT)
unnamed: C13.1, R44.2, R46.1, U7.9 (-IN), VR7.P$3 (A)
unnamed: C13.2, R45.1, U7.8 (OUT)
unnamed: OUT_2C.P$1_TIP (TIP), R45.2, R46.2
unnamed: R47.1, U7.2 (-IN), VR8.P$1 (E)
unnamed: R47.2, R48.1, U7.1 (OUT)
unnamed: C14.1, R48.2, R49.1, U7.13 (-IN), VR8.P$3 (A)
unnamed: C14.2, R50.1, U7.14 (OUT)
unnamed: OUT_2D.P$1_TIP (TIP), R49.2, R50.2
unnamed: R12.2, VR8.P$2 (S)
unnamed: R11.2, VR7.P$2 (S)
V+: C1.1, C3.1, C4.1, C20.1, C21.1, C22.1, C23.1, D1.C, U1.8 (V+), U2.4 (V+), U4.4 (V+), U5.4 (V+), U6.4 (V+), U7.4 (V+)
V-: C2.2, C6.2, C7.2, C15.2, C16.2, C17.2, C18.2, D2.A, U1.4 (V-), U2.11 (V-), U4.11 (V-), U5.11 (V-), U6.11 (V-), U7.11 (V-)

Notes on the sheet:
For prototype PCBs: Add wire between pin 1 of U7 and the bottom pad of R48
Revision 1-5 have inverting unity mixers. Resolved in Revision 6
